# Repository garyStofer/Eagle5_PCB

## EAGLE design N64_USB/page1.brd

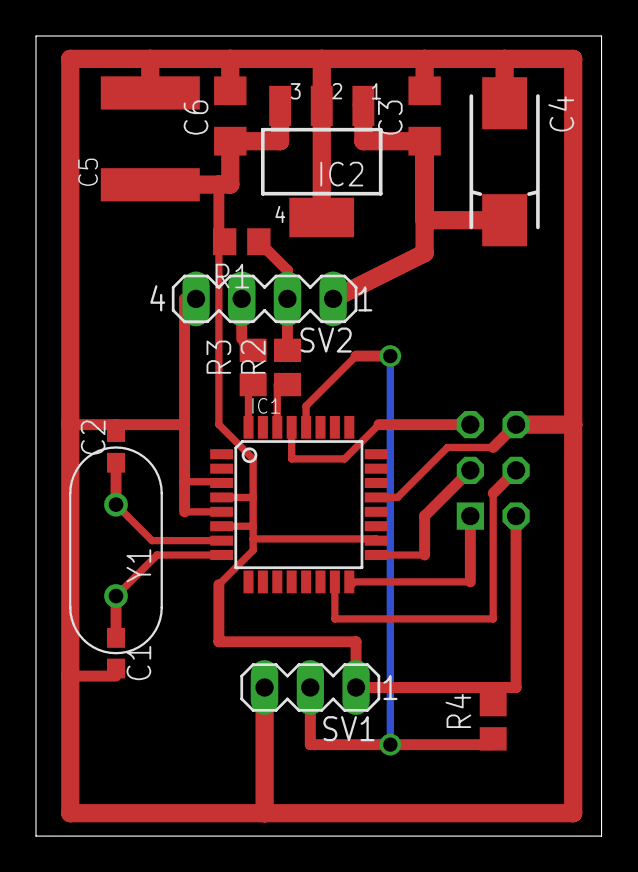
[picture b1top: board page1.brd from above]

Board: 2 copper layers, 31.4 x 44.4 mm, 16 parts (1 on the bottom side), 14 nets.

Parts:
C1, C2: 27p; C0603
C3, C6: 100n; C1206
C4: 10uf; 085CS_1AR
C5: 20u; C2220K
IC1: MEGA8-AI; TQFP32-08
IC2: 78M33; SOT223
J1: AVR-ISP-6
R1: 1.5k; R0805
R2, R3: 68; R0805
R4: 1K; R0805
SV1: MA03-1
SV2: MA04-1
Y1: 12Mhz; XTAL

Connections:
D+: R3.2, SV2.3
D-: R1.1, R2.2, SV2.2
GND: C1.2, C2.2, C3.2, C4.-, C5.2, C6.2, IC1.3, IC1.5, IC1.21, IC2.2, IC2.4, J1.6, SV1.3, SV2.4
MISO: IC1.16, J1.1
MOSI: IC1.15, J1.4
unnamed: C3.1, C4.+, IC2.1, SV2.1
unnamed: C2.1, IC1.7, Y1.P$2
unnamed: C1.1, IC1.8, Y1.P$1
unnamed: IC1.30, R2.1
unnamed: IC1.32, R3.1
unnamed: IC1.28, R4.1, SV1.2
RST: IC1.29, J1.5
SCK: IC1.17, J1.3
V3_3: C5.1, C6.1, IC1.4, IC1.6, IC1.18, IC2.3, J1.2, R1.2, R4.2, SV1.1

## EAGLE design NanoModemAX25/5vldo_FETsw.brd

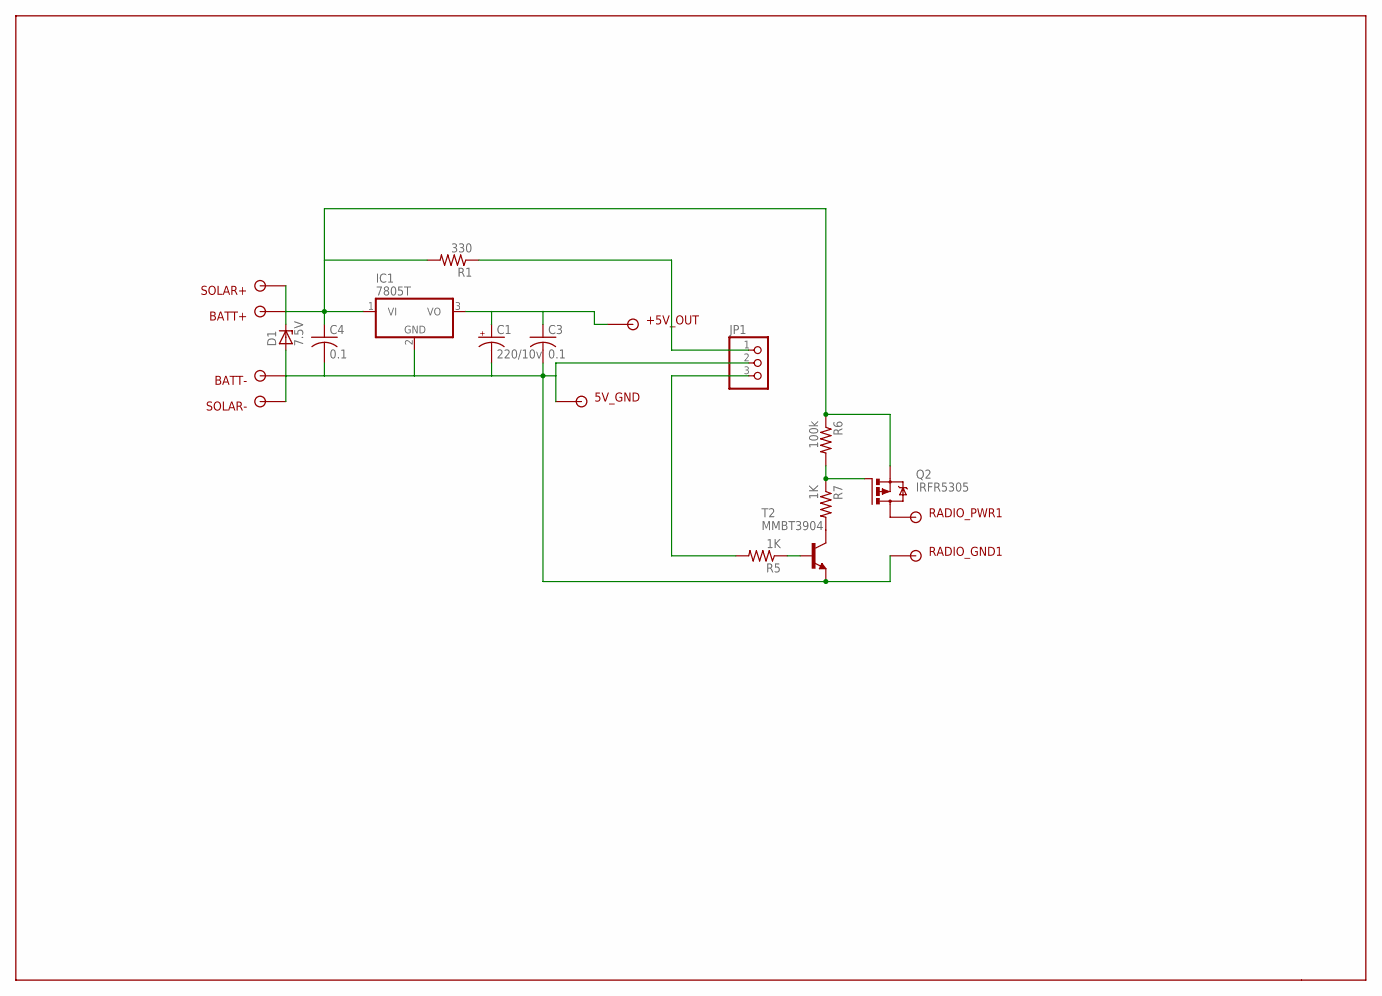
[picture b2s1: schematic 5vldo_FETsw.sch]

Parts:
5V_GND: SOLDER_POINTD; P1-17Y
+5V_OUT: SOLDER_POINTD; P1-17Y
BATT+: SOLDER_POINTD; P1-17Y
BATT-: SOLDER_POINTD; P1-17Y
C1: 220/10v; SMC_B
C3, C4: 0.1; C0805
D1: 7.5V; SMB
IC1: 7805T; TO220H
JP1: PINHD-1X3; 1X03
Q2: IRFR5305; D-PAK_TO252AA
R1: 330; R0603
R5, R7: 1K; R0603
R6: 100k; R0603
RADIO_GND1: SOLDER_POINTD; P1-17Y
RADIO_PWR1: SOLDER_POINTD; P1-17Y
SOLAR+: SOLDER_POINTD; P1-17Y
SOLAR-: SOLDER_POINTD; P1-17Y
T2: MMBT3904; SOT23-BEC

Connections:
unnamed: BATT+.1, C4.1, D1.C, IC1.1 (VI), Q2.3 (S), R1.2, R6.1, SOLAR+.1
unnamed: +5V_OUT.1, C1.+, C3.1, IC1.3 (VO)
unnamed: JP1.1, R1.1
unnamed: 5V_GND.1, BATT-.1, C1.-, C3.2, C4.2, D1.A, IC1.2 (GND), JP1.2, RADIO_GND1.1, SOLAR-.1, T2.E
unnamed: JP1.3, R5.2
unnamed: R5.1, T2.B
unnamed: R7.2, T2.C
unnamed: Q2.1 (G), R6.2, R7.1
unnamed: Q2.4 (D), RADIO_PWR1.1

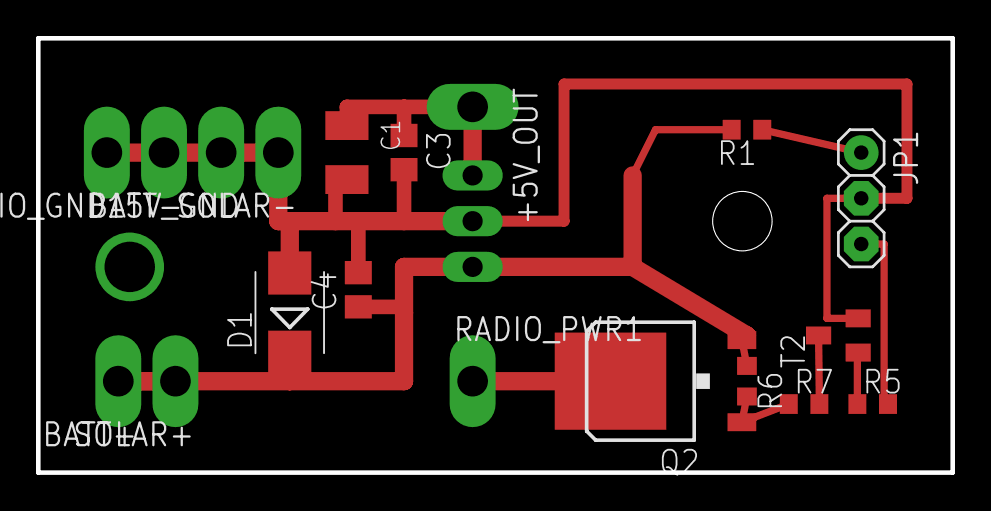
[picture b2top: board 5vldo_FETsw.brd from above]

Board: 2 copper layers, 50.8 x 24.1 mm, 20 parts (1 on the bottom side), 9 nets.

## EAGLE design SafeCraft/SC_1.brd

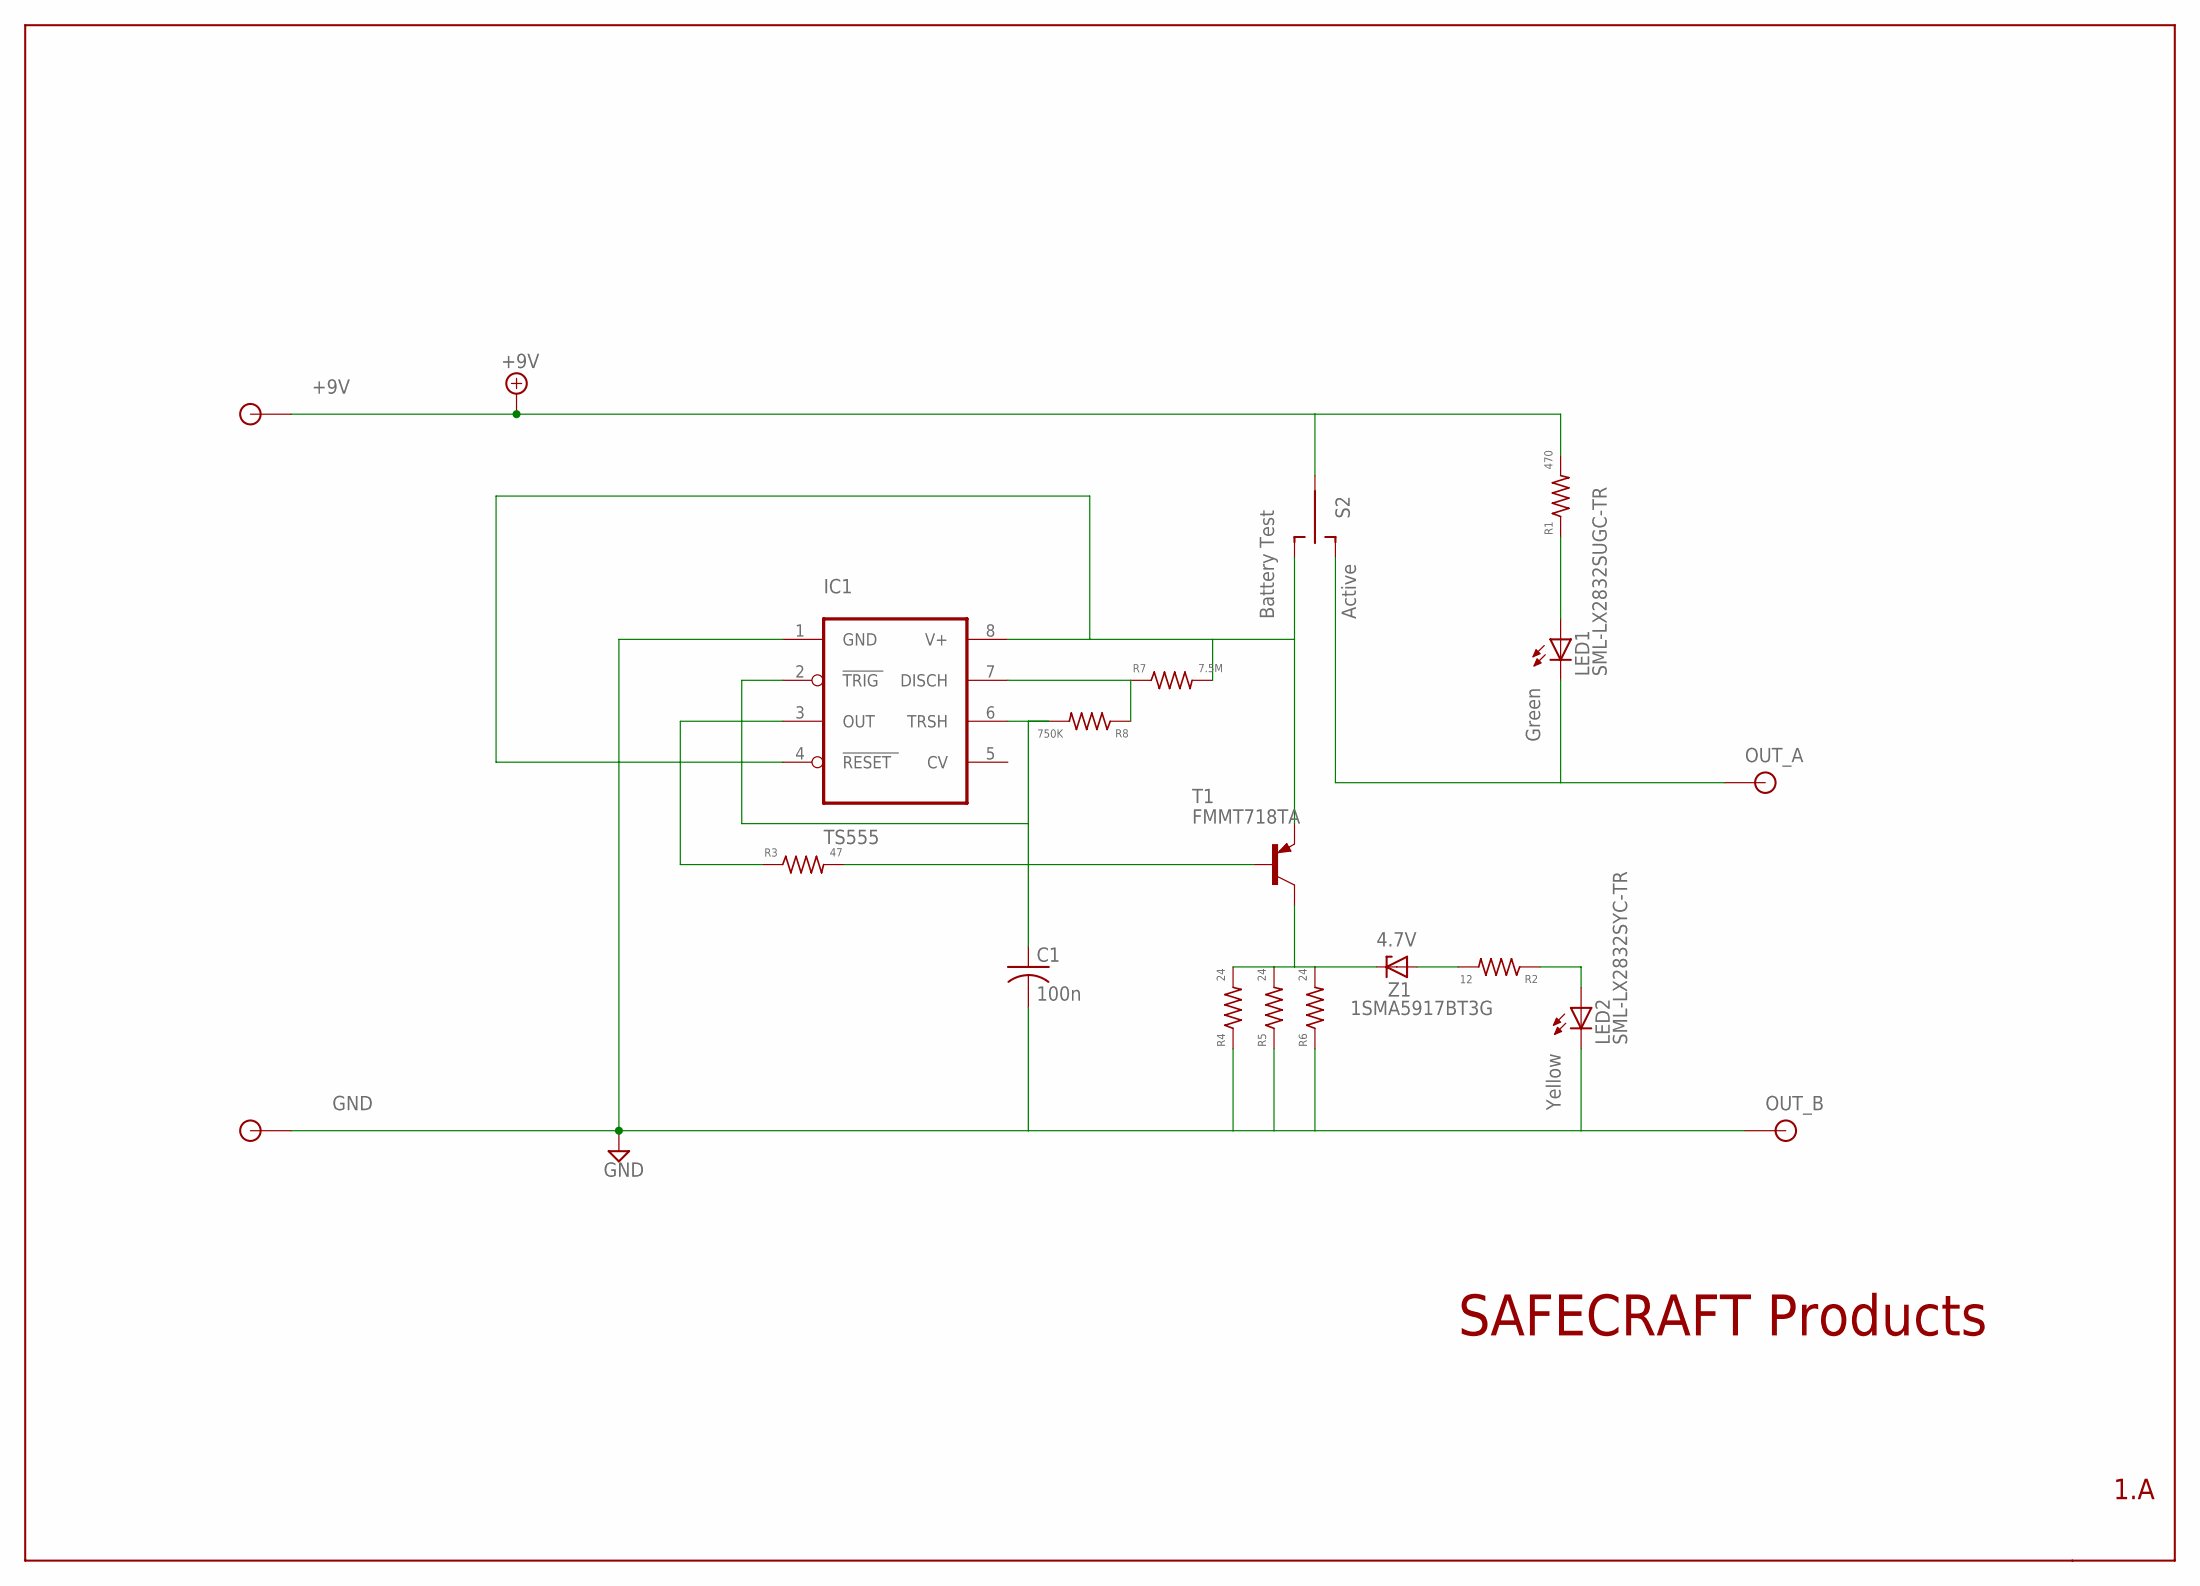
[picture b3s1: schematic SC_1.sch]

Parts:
C1: 100n; C0805
IC1: TS555; SO08
LED1: SML-LX2832SUGC-TR; P-LCC-2
LED2: SML-LX2832SYC-TR; P-LCC-2
R1: 470; R0805
R2: 12; R0805
R3: 47; R0805
R4, R5, R6: 24; R1206
R7: 7.5M; R0805
R8: 750K; R0805
S2: TL39POB; TL3XPO_NOHOLES
T1: FMMT718TA; SOT23-BEC
U$1, U$2, U$3, U$4: SOLDERPAD_NOHOLE; SOLDERPAD_NOHOLES
Z1: 1SMA5917BT3G; SMB

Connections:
+9V: R1.2, S2.P$2, U$3.P$1
GND: C1.2, IC1.1 (GND), LED2.C, R4.1, R5.1, R6.1, U$2.P$1, U$4.P$1
unnamed: IC1.4 (RESET), IC1.8 (V+), R7.2, S2.P$3 (S), T1.E
unnamed: R2.2, Z1.A
unnamed: LED1.A, R1.1
unnamed: C1.1, IC1.2 (TRIG), IC1.6 (TRSH), R8.2
unnamed: LED2.A, R2.1
unnamed: R3.2, T1.B
unnamed: IC1.3 (OUT), R3.1
unnamed: IC1.7 (DISCH), R7.1, R8.1
unnamed: R4.2, R5.2, R6.2, T1.C, Z1.C
OUT_A: LED1.C, S2.P$1 (O), U$1.P$1

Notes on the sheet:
Yellow
Green
Active
Battery Test
OUT_B
1.A
SAFECRAFT Products
4.7V

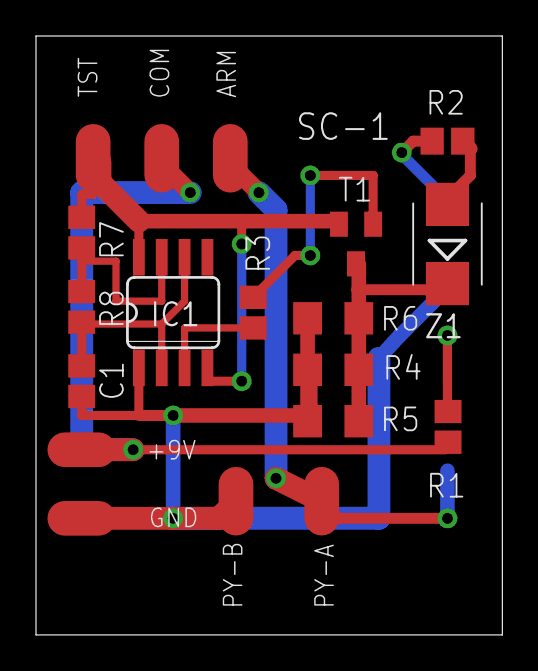
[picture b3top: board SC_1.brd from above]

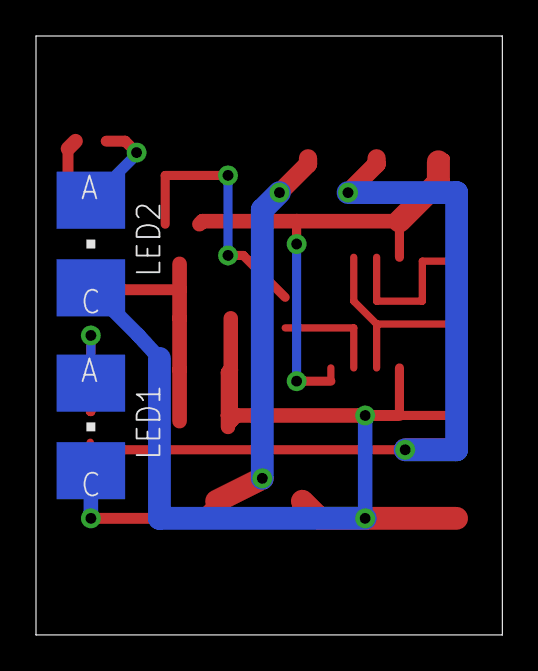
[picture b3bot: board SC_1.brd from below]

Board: 2 copper layers, 25.9 x 33.3 mm, 19 parts (2 on the bottom side), 12 nets.
